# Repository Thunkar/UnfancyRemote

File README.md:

# The Unfancy Remote

A cheap, open, modular and reliable DIY remote with a focus on RF performance. 

**WARNING** : The software and CAD files included in this repo are in a **BETA STAGE** at the moment and **SHOULD BE USED CAREFULLY**. I am not responsible for **ANY** injures or damages you may incur as a result of using the HW or SW described in this project.

# Design considerations

* Unfancy. I use other devices for my telemetry, so no UART (even though could be easily added in the future) or OLED screens. PPM for the win.
* DIY friendly and modular. 
* Stellar RF performance is a must. The whole idea for this project came after in the FPV drone space [this project](https://www.expresslrs.org/2.0/) became super popular. It uses LoRa transcievers to achieve great range and link speeds, using a proprietary modulation that is specially robust against interference. It can also work on 433MHz/868MHz/2.4GHz bands depending on the specific module.
* Multiple shells to accomodate thumbwheels, triggers, Qi charging, battery sizes...
* Community driven

# Building the code

It has been tested on the latest (at the time of writing, 1.8.19) Arduino IDE version, using the fantastic [SX12XX Library](https://github.com/StuartsProjects/SX12XX-LoRa) by StuartsProjects.

# Documentation

1) [Ordering](./docs/ordering.md)
2) [Soldering](./docs/soldering.md)
3) [Assembly](./docs/assembly.md)
4) [Software configuration](./docs/software.md)
5) [Remote operation](./docs/operation.md)

# Contributing

All contributions must go through a process of review and validation via a Pull Request before being integrated into the codebase. If you wish to contribute, please fork the repo, perform your modifications **TEST THEM** and submit a PR for review. The place to discuss bugs, new features or suggestions is the [esk8 news forum](https://forum.esk8.news/t/the-unfancy-remote-wip-diy-reliable-remote).

# License 
```
            DO WHAT THE FUCK YOU WANT TO PUBLIC LICENSE
                    Version 2, December 2004
 
 Copyright (C) 2022 Gregorio Juliana Quirós
  Madrid, Spain
 Everyone is permitted to copy and distribute verbatim or modified
 copies of this license document, and changing it is allowed as long
 as the name is changed.
 
            DO WHAT THE FUCK YOU WANT TO PUBLIC LICENSE
   TERMS AND CONDITIONS FOR COPYING, DISTRIBUTION AND MODIFICATION
 
  0. You just DO WHAT THE FUCK YOU WANT TO.
  ```

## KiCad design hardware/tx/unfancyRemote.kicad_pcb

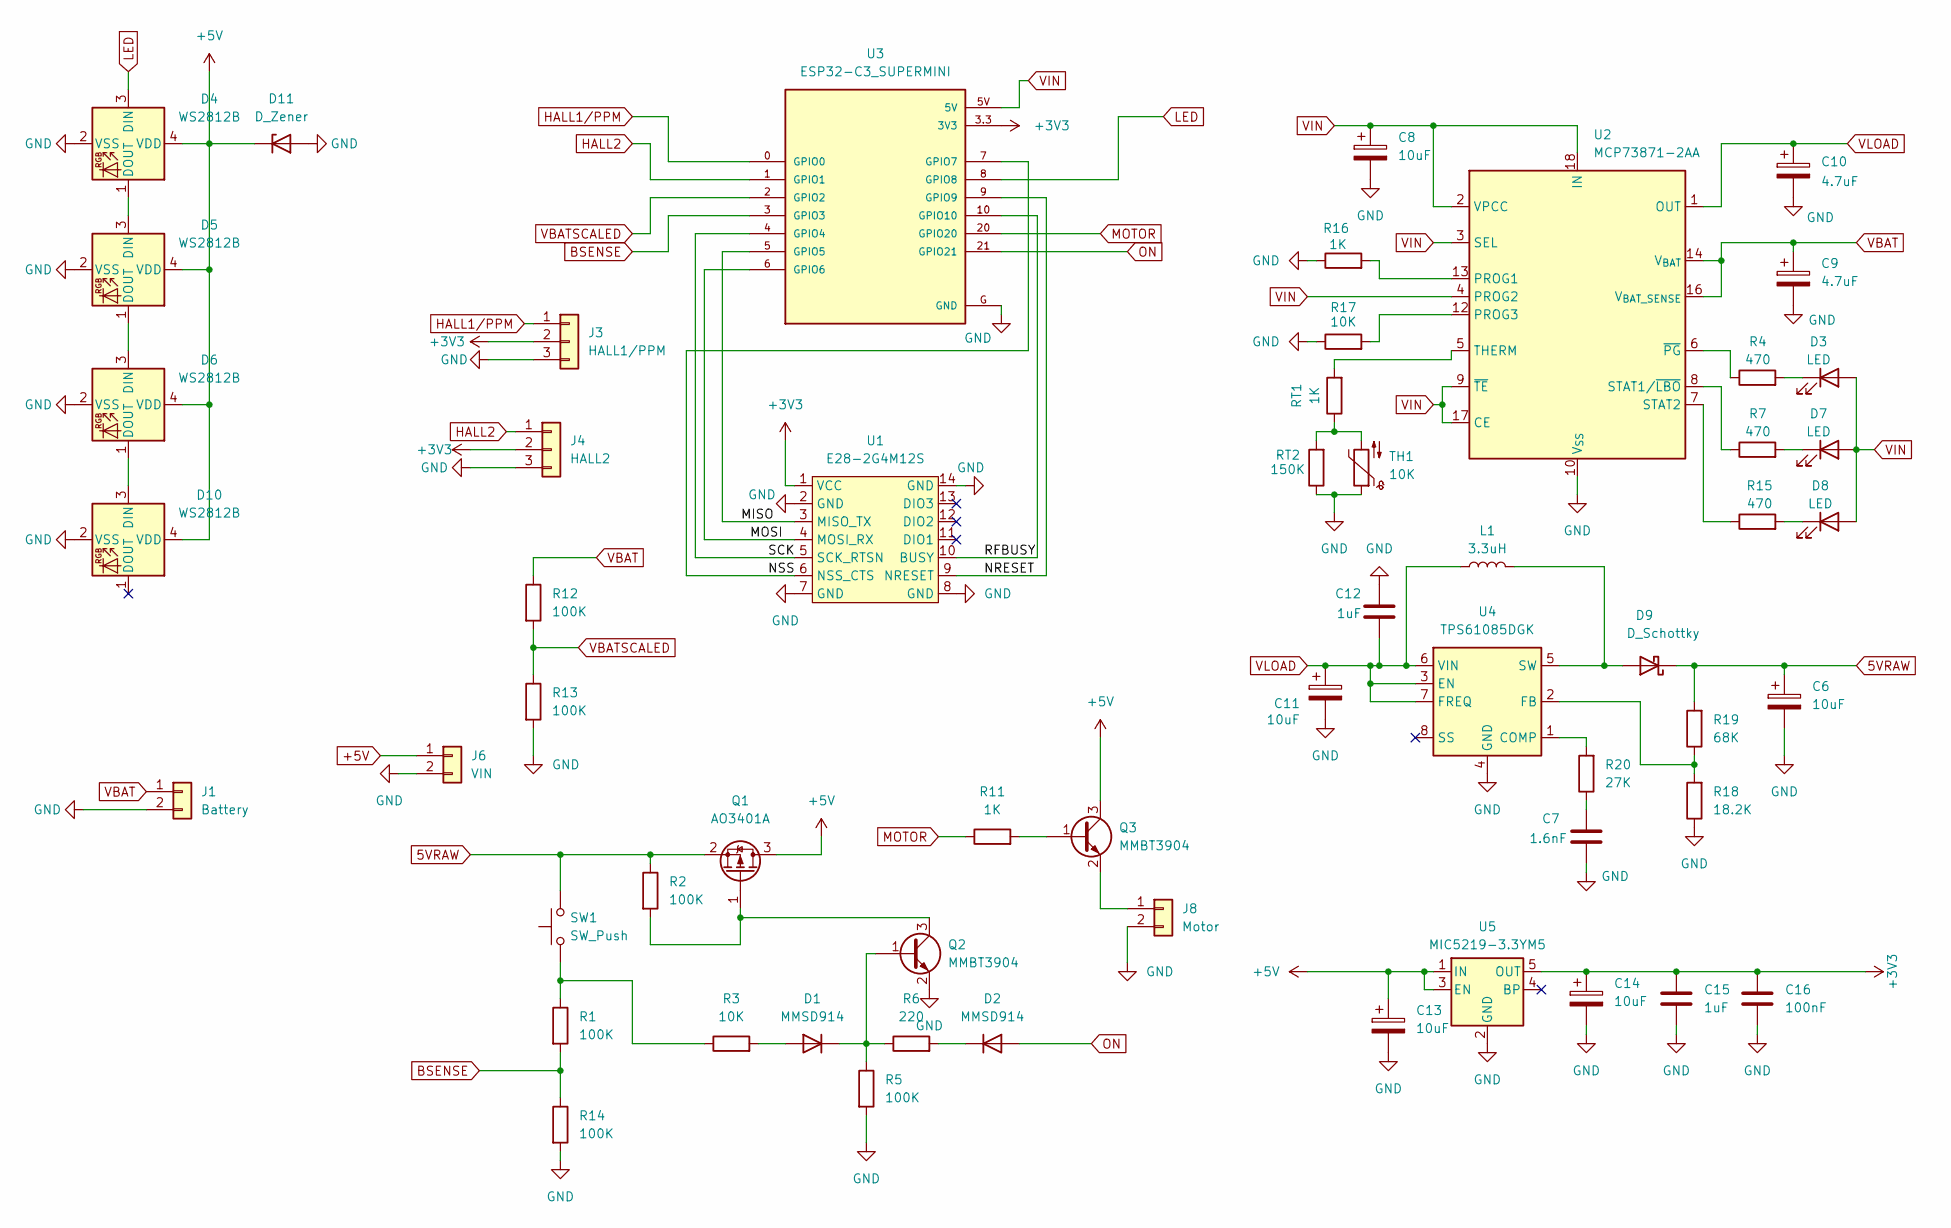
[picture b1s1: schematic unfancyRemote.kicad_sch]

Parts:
C6, C8, C11, C13, C14: 10uF; CP_EIA-3216-10_Kemet-I; LCSC C119051
C7: 1.6nF; C_0603_1608Metric; LCSC C437532
C9, C10: 4.7uF; CP_EIA-3216-10_Kemet-I; LCSC C123256
C12, C15: 1uF; C_0402_1005Metric; LCSC C52923
C16: 100nF; C_0402_1005Metric; LCSC C307331
D1, D2: MMSD914; D_SOD-123; LCSC C21508
D3, D7, D8: LED; LED_0805_2012Metric; LCSC C84256
D4, D5, D6, D10: WS2812B; LED_WS2812B-2020_PLCC4_2.0x2.0mm; LCSC C965555
D9: D_Schottky; D_SOD-523; LCSC C413992
D11: D_Zener; D_SOD-123
J1: Battery; PinHeader_1x02_P2.00mm_Vertical
J3: HALL1/PPM; SolderWirePad_1x03_SMD_1x2mm
J4: HALL2; SolderWirePad_1x03_SMD_1x2mm
J6: VIN; SolderWirePad_1x02_SMD_1x2mm
J8: Motor; SolderWirePad_1x02_SMD_1x2mm
L1: 3.3uH; L_Cenker_CKCS201610; LCSC C696469
Q1: AO3401A; SOT-23; LCSC C700954
Q2, Q3: MMBT3904; SOT-23; LCSC C20526
R1, R2, R5, R12, R14: 100K; R_0402_1005Metric; LCSC C25741
R3, R17: 10K; R_0402_1005Metric; LCSC C25744
R4, R7, R15: 470; R_0402_1005Metric; LCSC C25117
R6: 220; R_0402_1005Metric; LCSC C25091
R11, R16: 1K; R_0402_1005Metric; LCSC C11702
R13: 100K; R_0402_1005Metric; LCSC C407725
R18: 18.2K; R_0402_1005Metric; LCSC C25859
R19: 68K; R_0402_1005Metric; LCSC C482226
R20: 27K; R_0402_1005Metric; LCSC C284471
RT1: 1K; R_0402_1005Metric; LCSC C11702
RT2: 150K; R_0402_1005Metric; LCSC C407748
SW1: SW_Push; SW_SPST_PTS645; LCSC C393947
TH1: 10K; R_0402_1005Metric; LCSC C700818
U1: E28-2G4M12S
U2: MCP73871-2AA; QFN-20-1EP_4x4mm_P0.5mm_EP2.5x2.5mm; LCSC C144351
U3: ESP32-C3_SUPERMINI; MODULE_ESP32-C3_SUPERMINI
U4: TPS61085DGK; VSSOP-8_3x3mm_P0.65mm; LCSC C113659
U5: MIC5219-3.3YM5; SOT-23-5; LCSC C29613

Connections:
5VRAW: C6.1, D9.1 (K), Q1.2 (S), R2.1, R19.2, SW1.2
+3V3: C14.1, C15.1, C16.1, J3.2, J4.2, U1.1 (VCC), U3.3.3 (3V3), U5.5 (OUT)
+5V: C13.1, D4.4 (VDD), D5.4 (VDD), D6.4 (VDD), D10.4 (VDD), D11.1 (K), J6.1, Q1.3 (D), Q3.3 (C), U5.1 (IN), U5.3 (EN)
/MISO: U1.3 (MISO_TX), U3.5 (GPIO5)
/MOSI: U1.4 (MOSI_RX), U3.6 (GPIO6)
/NRESET: U1.9 (NRESET), U3.9 (GPIO9)
/NSS: U1.6 (NSS_CTS), U3.7 (GPIO7)
/RFBUSY: U1.10 (BUSY), U3.10 (GPIO10)
/SCK: U1.5 (SCK_RTSN), U3.4 (GPIO4)
BSENSE: R1.2, R14.1, U3.3 (GPIO3)
GND: C6.2, C7.2, C8.2, C9.2, C10.2, C11.2, C12.1, C13.2, C14.2, C15.2, C16.2, D4.2 (VSS), D5.2 (VSS), D6.2 (VSS), D10.2 (VSS), D11.2 (A), J1.2, J3.3, J4.3, J6.2, J8.2, Q2.2 (E), R5.2, R13.2, R14.2, R16.1, R17.1, R18.1, RT2.1, TH1.1, U1.2 (GND), U1.7 (GND), U1.8 (GND), U1.14 (GND), U2.10 (V_{SS}), U2.11 (V_{SS}), U2.21 (V_{SS}), U3.G (GND), U4.4 (GND), U5.2 (GND)
HALL1/PPM: J3.1, U3.0 (GPIO0)
HALL2: J4.1, U3.1 (GPIO1)
LED: D4.3 (DIN), U3.8 (GPIO8)
MOTOR: R11.1, U3.20 (GPIO20)
unnamed: C7.1, R20.1
unnamed: D1.2 (A), R3.2
unnamed: D1.1 (K), Q2.1 (B), R5.1, R6.1
unnamed: D2.1 (K), R6.2
unnamed: D3.1 (K), R4.2
unnamed: D4.1 (DOUT), D5.3 (DIN)
unnamed: D5.1 (DOUT), D6.3 (DIN)
unnamed: D7.1 (K), R7.2
unnamed: D8.1 (K), R15.2
unnamed: D9.2 (A), L1.2, U4.5 (SW)
unnamed: D6.1 (DOUT), D10.3 (DIN)
unnamed: J8.1, Q3.2 (E)
unnamed: Q1.1 (G), Q2.3 (C), R2.2
unnamed: Q3.1 (B), R11.2
unnamed: R1.1, R3.1, SW1.1
unnamed: RT1.1, RT2.2, TH1.2
unnamed: R16.2, U2.13 (PROG1)
unnamed: R17.2, U2.12 (PROG3)
unnamed: R7.1, U2.8 (STAT1/~LBO)
unnamed: R15.1, U2.7 (STAT2)
unnamed: RT1.2, U2.5 (THERM)
unnamed: R4.1, U2.6 (~PG)
unnamed: R20.2, U4.1 (COMP)
unnamed: R18.2, R19.1, U4.2 (FB)
ON: D2.2 (A), U3.21 (GPIO21)
VBAT: C9.1, J1.1, R12.1, U2.14 (V_{BAT}), U2.15 (V_{BAT}), U2.16 (V_{BAT_SENSE})
VBATSCALED: R12.2, R13.1, U3.2 (GPIO2)
VIN: C8.1, D3.2 (A), D7.2 (A), D8.2 (A), U2.2 (VPCC), U2.3 (SEL), U2.4 (PROG2), U2.9 (~TE), U2.17 (CE), U2.18 (IN), U2.19 (IN), U3.5V
VLOAD: C10.1, C11.1, C12.2, L1.1, U2.1 (OUT), U2.20 (OUT), U4.3 (EN), U4.6 (VIN), U4.7 (FREQ)

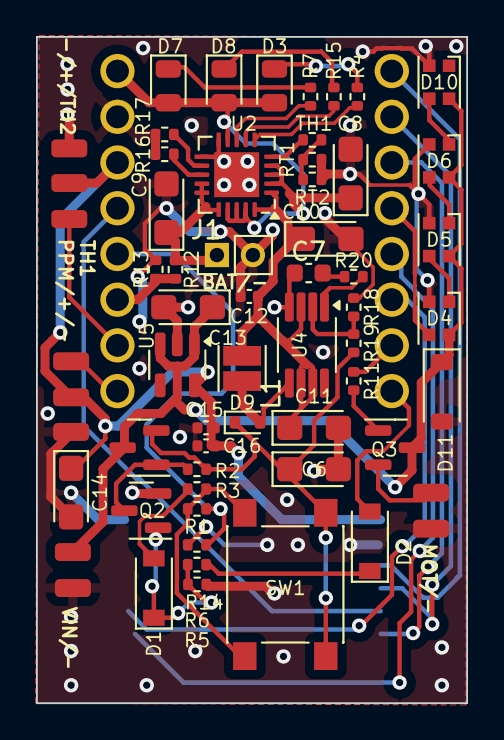
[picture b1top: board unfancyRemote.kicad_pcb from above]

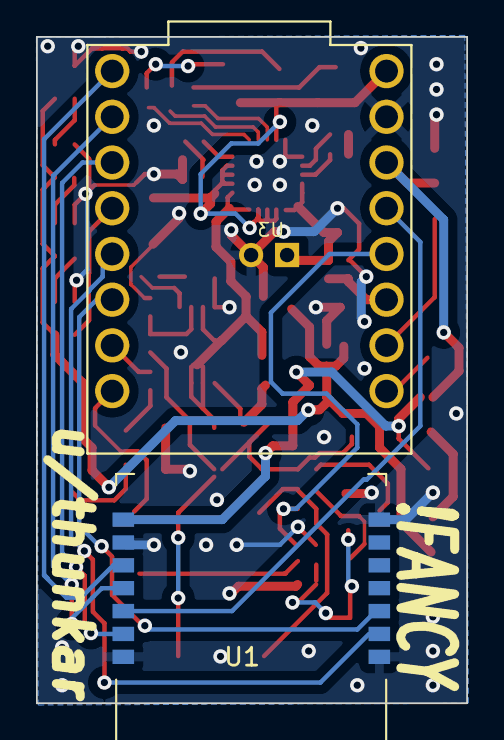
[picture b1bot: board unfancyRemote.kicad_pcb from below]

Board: 2 copper layers, 23.9 x 37.0 mm, 57 parts (2 on the bottom side), 44 nets.

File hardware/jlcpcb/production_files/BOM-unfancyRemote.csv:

Comment,Designator,Footprint,LCSC,Quantity
TPS61085DGK,U4,VSSOP-8_3x3mm_P0.65mm,C113659,1
1K,"R11,R16,RT1",R_0402_1005Metric,C11702,3
10uF,"C11,C13,C14,C6,C8",CP_EIA-3216-10_Kemet-I,C119051,5
4.7uF,"C10,C9",CP_EIA-3216-10_Kemet-I,C123256,2
MCP73871-2AA,U2,QFN-20-1EP_4x4mm_P0.5mm_EP2.5x2.5mm,C144351,1
MMBT3904,"Q2,Q3",SOT-23,C20526,2
MMSD914,"D1,D2",D_SOD-123,C21508,2
220,R6,R_0402_1005Metric,C25091,1
470,"R15,R4,R7",R_0402_1005Metric,C25117,3
100K,"R1,R12,R14,R2,R5",R_0402_1005Metric,C25741,5
10K,"R17,R3",R_0402_1005Metric,C25744,2
18.2K,R18,R_0402_1005Metric,C25859,1
27K,R20,R_0402_1005Metric,C284471,1
MIC5219-3.3YM5,U5,SOT-23-5,C29613,1
100nF,C16,C_0402_1005Metric,C307331,1
SW_Push,SW1,SW_SPST_PTS645,C393947,1
6.8K,R13,R_0402_1005Metric,C407725,1
150K,RT2,R_0402_1005Metric,C407748,1
D_Schottky,D9,D_SOD-523,C413992,1
1.6nF,C7,C_0603_1608Metric,C437532,1
68K,R19,R_0402_1005Metric,C482226,1
1uF,"C12,C15",C_0402_1005Metric,C52923,2
3.3uH,L1,L_Cenker_CKCS201610,C696469,1
10K,TH1,R_0402_1005Metric,C700818,1
AO3401A,Q1,SOT-23,C700954,1
LED,"D3,D7,D8",LED_0805_2012Metric,C84256,3
WS2812B,"D10,D4,D5,D6",LED_WS2812B-2020_PLCC4_2.0x2.0mm,C965555,4
E28-2G4M12S,U1,E28-2G4M12S,,1
Battery,J1,PinHeader_1x02_P2.00mm_Vertical,,1
VIN,J6,SolderWirePad_1x02_SMD_1x2mm,,1
HALL1/PPM,J3,SolderWirePad_1x03_SMD_1x2mm,,1
HALL2,J4,SolderWirePad_1x03_SMD_1x2mm,,1
Motor,J8,SolderWirePad_1x02_SMD_1x2mm,,1
ESP32-C3_SUPERMINI,U3,MODULE_ESP32-C3_SUPERMINI,,1

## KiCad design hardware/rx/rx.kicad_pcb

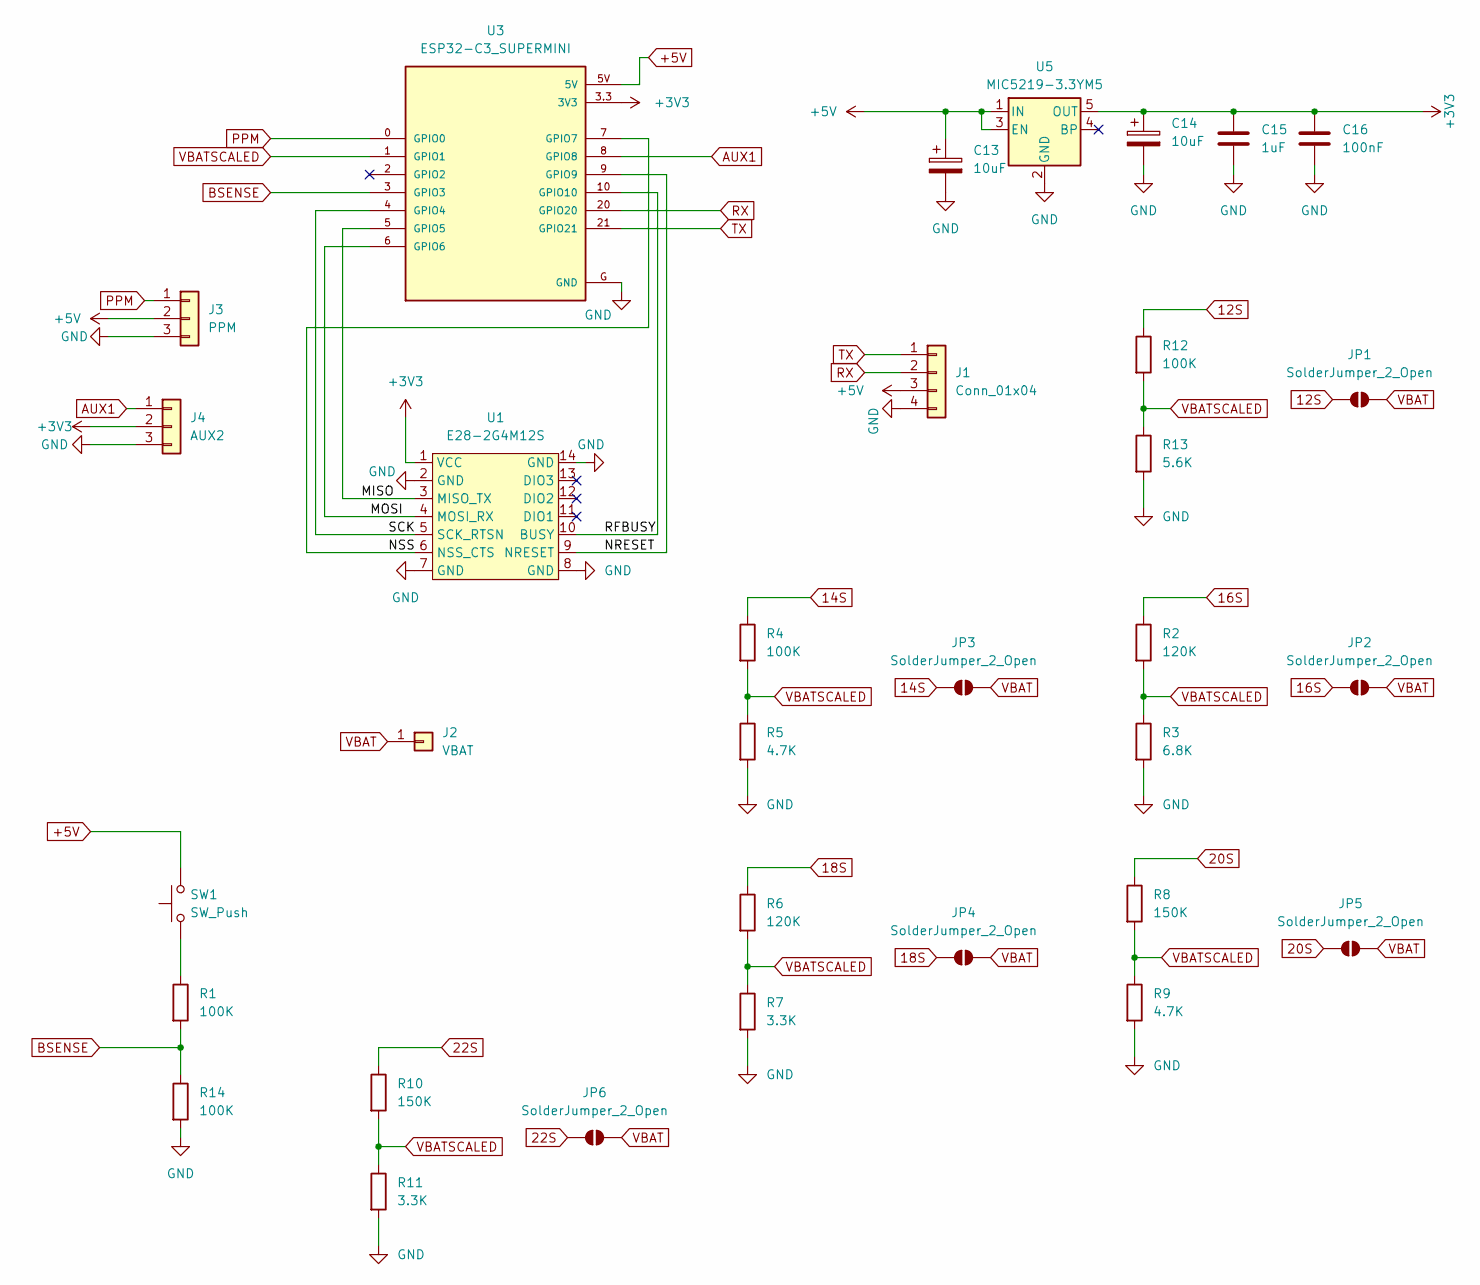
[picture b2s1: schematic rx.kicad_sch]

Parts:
C13, C14: 10uF; CP_EIA-3216-10_Kemet-I; LCSC C119051
C15: 1uF; C_0402_1005Metric; LCSC C52923
C16: 100nF; C_0402_1005Metric; LCSC C307331
J1: Conn_01x04; SolderWirePad_1x04_SMD_1x2mm
J2: VBAT; SolderWirePad_1x01_SMD_1x2mm
J3: PPM; SolderWirePad_1x03_SMD_1x2mm
J4: AUX2; SolderWirePad_1x03_SMD_1x2mm
JP1, JP2, JP3, JP4, JP5, JP6: SolderJumper_2_Open; SolderJumper-2_P1.3mm_Open_RoundedPad1.0x1.5mm
R1, R4, R12, R14: 100K; R_0402_1005Metric; LCSC C25741
R2, R6: 120K; R_0402_1005Metric; LCSC C25741
R3: 6.8K; R_0402_1005Metric; LCSC C407725
R5, R9: 4.7K; R_0402_1005Metric; LCSC C407725
R7, R11: 3.3K; R_0402_1005Metric; LCSC C407725
R8, R10: 150K; R_0402_1005Metric; LCSC C25741
R13: 5.6K; R_0402_1005Metric; LCSC C407725
SW1: SW_Push; SW_SPST_PTS645; LCSC C393947
U1: E28-2G4M12S
U3: ESP32-C3_SUPERMINI; MODULE_ESP32-C3_SUPERMINI
U5: MIC5219-3.3YM5; SOT-23-5; LCSC C29613

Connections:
12S: JP1.1 (A), R12.1
14S: JP3.1 (A), R4.1
16S: JP2.1 (A), R2.1
18S: JP4.1 (A), R6.1
20S: JP5.1 (A), R8.1
22S: JP6.1 (A), R10.1
+3V3: C14.1, C15.1, C16.1, J4.2, U1.1 (VCC), U3.3.3 (3V3), U5.5 (OUT)
+5V: C13.1, J1.3, J3.2, SW1.2, U3.5V, U5.1 (IN), U5.3 (EN)
/MISO: U1.3 (MISO_TX), U3.5 (GPIO5)
/MOSI: U1.4 (MOSI_RX), U3.6 (GPIO6)
/NRESET: U1.9 (NRESET), U3.9 (GPIO9)
/NSS: U1.6 (NSS_CTS), U3.7 (GPIO7)
/RFBUSY: U1.10 (BUSY), U3.10 (GPIO10)
/SCK: U1.5 (SCK_RTSN), U3.4 (GPIO4)
AUX1: J4.1, U3.8 (GPIO8)
BSENSE: R1.2, R14.1, U3.3 (GPIO3)
GND: C13.2, C14.2, C15.2, C16.2, J1.4, J3.3, J4.3, R3.2, R5.2, R7.2, R9.2, R11.2, R13.2, R14.2, U1.2 (GND), U1.7 (GND), U1.8 (GND), U1.14 (GND), U3.G (GND), U5.2 (GND)
unnamed: R1.1, SW1.1
PPM: J3.1, U3.0 (GPIO0)
RX: J1.2, U3.20 (GPIO20)
TX: J1.1, U3.21 (GPIO21)
VBAT: J2.1, JP1.2 (B), JP2.2 (B), JP3.2 (B), JP4.2 (B), JP5.2 (B), JP6.2 (B)
VBATSCALED: R2.2, R3.1, R4.2, R5.1, R6.2, R7.1, R8.2, R9.1, R10.2, R11.1, R12.2, R13.1, U3.1 (GPIO1)

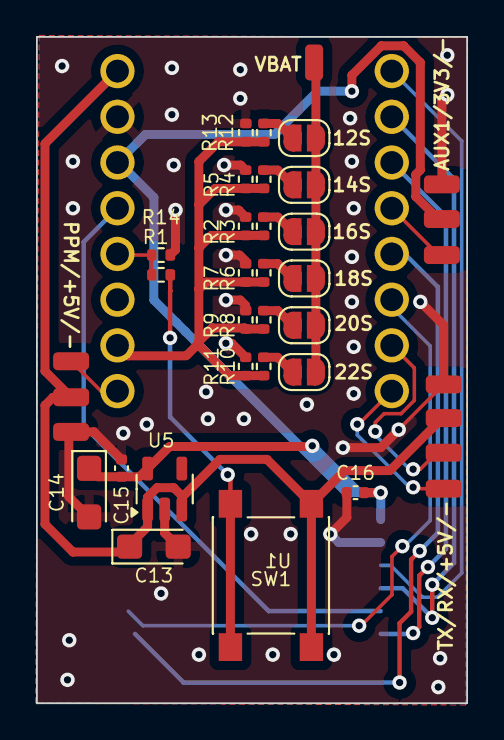
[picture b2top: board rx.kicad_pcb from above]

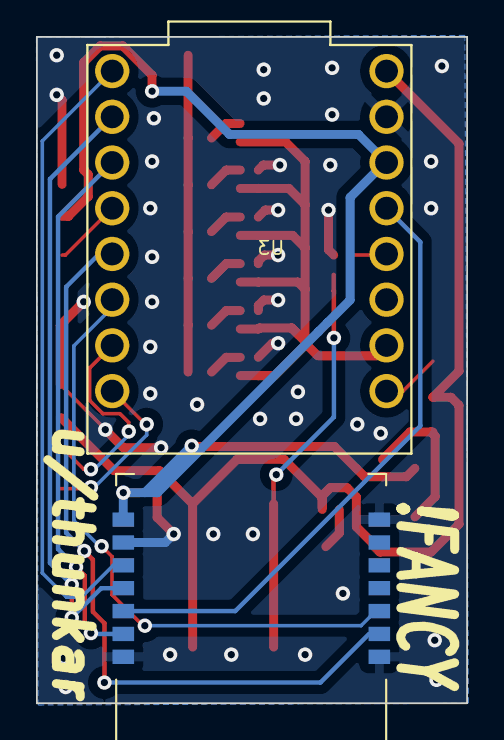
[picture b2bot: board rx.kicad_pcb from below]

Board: 2 copper layers, 23.9 x 37.0 mm, 32 parts (2 on the bottom side), 23 nets.

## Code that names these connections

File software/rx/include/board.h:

#pragma once

// Log to serial
#define DEBUG

// RF params

#define CH_BANDWIDTH_HZ 2500000
#define BASE_FREQUENCY 2400000000

// HW Pins

const int NSS = 7;                           //select on LoRa device
const int NRESET = 9;                        //reset on LoRa device
const int RFBUSY = 10;                        //RF busy on LoRa device 
const int DIO1 = -1;                          //DIO1 on LoRa device, used for RX and TX done
const int DIO2 = -1;                         //DIO2 on LoRa device, normally not used so set to -1
const int DIO3 = -1;                         //DIO3 on LoRa device, normally not used so set to -1
const int RX_EN = -1;                        //pin for RX enable, used on some SX1280 devices, set to -1 if not used
const int TX_EN = -1;                        //pin for TX enable, used on some SX1280 devices, set to -1 if not used

const int BUTTON = 3;
const int PPM = 0;
const int LED = 8;
const int VBAT = 1;   

// Constants

const unsigned long R2 = 5100;
const unsigned long R1 = 100000;

const unsigned int ENCODED_MAX = 4095;
const unsigned int ENCODED_HALF = 2048;

const unsigned int ADC_SAMPLES = 5;

// Time in us to hold the button to enter setup mode

const int SETUP_MODE_DELAY = 5000 * 1e3; 

// Scheduler

const int N_TASKS = 8;
struct TaskResult {
    bool success;
};

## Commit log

2022-02-25 Added kicad project for prototype hw
2022-02-27 Fixed R and Cs footprint
2022-02-27 Added gitignore
2022-03-06 Added dual trigger version
2022-03-09 Power button support in sw
2022-03-09 WIP 1.0
2022-03-09 Updated LoRa footprint
2022-03-10 Updates to PCB v1.0, simple disconnect detection on the remote
2022-03-11 Centering in software
2022-03-19 Added library, PCB 1.0, software scheduler
2022-03-20 Updated thumbwheel design
2022-03-20 WIP modes
2022-03-22 Software v1.0 for rx and tx
2022-03-23 Fixes and rudimentary TM
2022-03-27 Software V1 with TM and failsafe
2022-03-28 WIP thumbwheel case v1
2022-04-01 Fixed rx, beefier case
2022-04-01 Calibration
2022-04-02 Improved transmission stability
2022-04-04 Round version, PCB 2.0
2022-04-08 Pictures for the mini version
2022-04-11 PCB improvements, round version, cal procedure
2022-04-18 rx string to program memory
2022-04-27 Dual trigger support and better calibration
2022-04-29 CAD dump of all versions
2022-05-02 Added BOM
2022-05-09 Channel implementation
2022-05-10 Updated CAD files, added misc, updated BOM, basic pairing
2022-05-10 Added connection diagram
2022-05-12 Code cleanup, avoid overflow
2022-05-13 Added frequency debug
2022-05-14 Added PCBv2 model
2022-05-15 Forced standby after timeout
2022-05-15 PCB v2 gerber and bom
2022-06-15 Preparing sw compatibity with pcb v2
2022-06-16 Updated for PCB v2
2022-06-23 Started docs and manuals
2022-06-28 Added LM4040 as ext vref
2022-06-28 More docs
2022-07-03 Completed first version of documentation
2022-07-03 Fixed links
2022-07-16 Hopefully squashed lock bug
2022-07-16 Some rewording, removed .vscode folder
2022-07-16 Improved connection stability and tx/rx handover
2022-08-17 CAD dump
2022-08-17 Removed unnecesary file
2022-08-23 Force mode change on low remote battery, safer thresholds
2023-07-26 Added battery measurement average (2 samples)
2024-07-26 wip, kicad v8
2024-10-27 finished charging ic wiring
2024-11-18 power progress
2024-11-18 routing
2024-11-25 more routing
2025-01-11 working tx
2025-01-25 software progress
2025-01-25 don't lose docs
2025-01-25 refactor
2025-01-30 working http
2025-02-20 progress
2025-02-22 saving settings
2025-02-22 ready for calibration
2025-02-23 progress in calibration
2025-02-23 performance!
2025-02-23 UX improvements
2025-03-01 cleanup hw
2025-03-01 rx PCB
2025-03-02 update to kicad 9
2025-03-03 rx improvements
2025-03-06 ready for rx refactor
2025-03-08 rx refactor
2025-03-08 rx progress
2025-03-08 working everything
2025-03-08 adc sampling
2025-03-08 removed .vscode folder
2025-03-08 cleanup
2025-03-08 better encoding
2025-03-09 improvements
2025-03-09 cleaner explanations
2025-03-09 removed SNR and RSSI from tm
2025-03-09 default disconnected
2025-03-09 rock solid
2025-03-10 reconcile
2025-03-10 back to sync
2025-03-10 got timings right
2025-03-16 fixes
2025-03-16 tighter timings
2025-03-17 adjustments
2025-03-19 improved stability
2025-03-20 saner timeouts
2025-03-23 sw refactor, better reliability. Space out leds on the board, increase trace sizes
2025-03-23 optimize all the things
2025-03-23 jitter logging, 100Hz
2025-03-30 new adaptive scheduler
2025-04-01 tuned params
2025-04-02 simplified
2025-04-16 cleanup and fixes
2025-04-18 computed stats, web fixes
2025-06-04 prioritize rx above all else
2025-06-08 better throttle sampling
2025-06-28 param adjustments
2025-06-30 very late
2025-07-02 async rework
2025-07-03 more tasks refactor
2025-07-06 tx commands setup mode
2025-07-07 simplified scheduler
